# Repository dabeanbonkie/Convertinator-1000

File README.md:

# Convertinator 1000 Showcase

# Description
The Convertinator 1000 is a basic power supply that converts voltage from a USB-C (5V) to 1.2V, 3.3V, 12V & 24V, also featuring an output for 5V. It has the input as the USB-C and the outputs as dupont headers as its main use is for prototyping small cicuits and basic breadboarding. It isnt made to handle strong current but the 12V & 24V connections should be able to handle a bit more.

# Reason
I designed this as a project that i could maybe use in the future when doing smaller projects as i get more and more proficient in hardware. Its not intended to run anything too heavy but can handle basic circuitly which is all I would need it for. It also worked perfectly as a project to do while parts for other projects were printing.

# Usage
To use the Convertinator 1000, take a USB-C plugged into any socket (as long as it supplies 5V) and plug it into the USB-C component on the Convertinator 1000. From there, take two dupont wires and connect them to the two headers for each voltage. One header is for the output voltage which on each connection is the header on the left, and the other is the ground which is always on the right. I highly advise you NOT to run anything above 1A on the 1.2V, 3.3V & 5V headers and NOT anything above 1.8A on the 12V & 24V headers.

# Assembly
Putting all the parts together is easy as can be. Since i figured this power supply wouldnt be moving much i havent mounted the pcb. So to assemble the Convertinator 1000, just print both components, put the pcb in the shell making sure all the gubbins on the bottom of the pcb cleanly fit into the groves on the bottom of the shell. Then mount the lid to the shell using a simple nut and bolt (4.8 mm) on the mounting holes on both parts. Then its all complete.

Here is how the pcb should be placed from the bottom of the shell:

# PCB schematic

# PCB editor 

# Onshape Link
https://cad.onshape.com/documents/8818f429682032fa239a6543/w/3c67bc1c1aed2304218f7515/e/04401e7b527ba54e698f04d5?renderMode=0&uiState=6a372eb3d7346ceef4239fb8

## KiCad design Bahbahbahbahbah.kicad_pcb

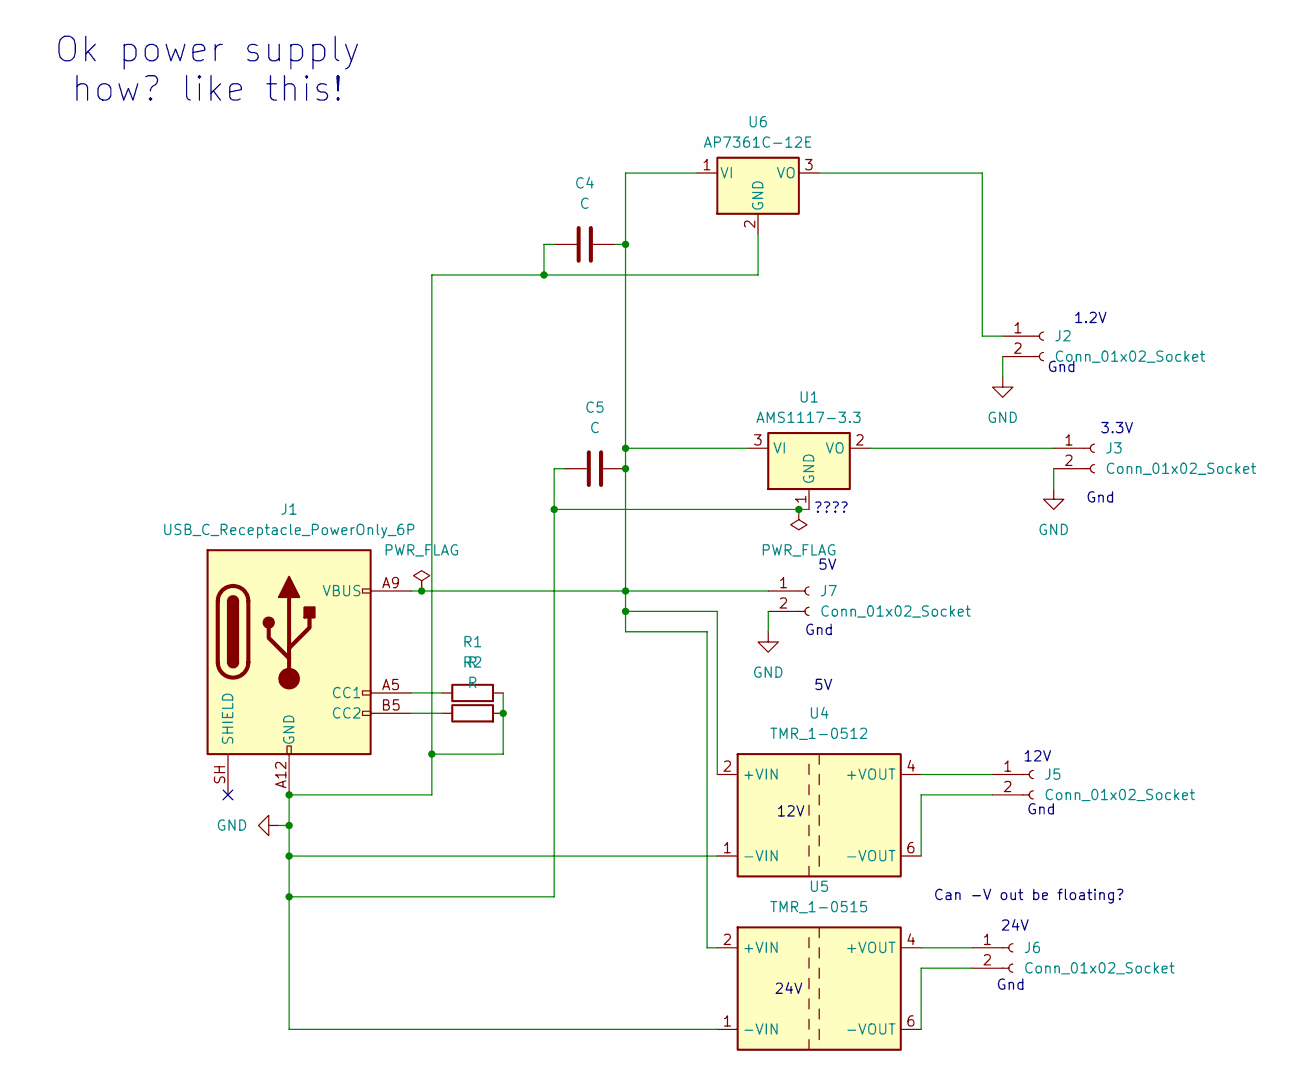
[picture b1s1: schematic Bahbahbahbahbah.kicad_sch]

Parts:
C4, C5: C; C_0402_1005Metric
J1: USB_C_Receptacle_PowerOnly_6P; USB_C_Receptacle_GCT_USB4125-xx-x-0190_6P_TopMnt_Horizontal
J2, J3, J5, J6, J7: Conn_01x02_Socket; PinSocket_1x02_P2.54mm_Horizontal
R1, R2: R; R_0402_1005Metric
U1: AMS1117-3.3; SOT-223-3_TabPin2
U4: TMR_1-0512; Converter_DCDC_TRACO_TMR-1-xxxx_Single_THT
U5: TMR_1-0515; Converter_DCDC_TRACO_TMR-1-xxxx_Single_THT
U6: AP7361C-12E; SOT-223-3_TabPin2

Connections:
GND: C4.1, C5.1, J1.A12 (GND), J1.B12 (GND), J2.2, J3.2, J7.2, R1.2, R2.2, U1.1 (GND), U4.1 (-VIN), U5.1 (-VIN), U6.2 (GND)
unnamed: J1.A5 (CC1), R1.1
unnamed: J1.B5 (CC2), R2.1
unnamed: J2.1, U6.3 (VO)
unnamed: J3.1, U1.2 (VO)
unnamed: J5.1, U4.4 (+VOUT)
unnamed: J5.2, U4.6 (-VOUT)
unnamed: J6.1, U5.4 (+VOUT)
unnamed: J6.2, U5.6 (-VOUT)
unnamed: C4.2, C5.2, J1.A9 (VBUS), J1.B9 (VBUS), J7.1, U1.3 (VI), U4.2 (+VIN), U5.2 (+VIN), U6.1 (VI)

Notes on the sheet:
Can -V out be floating?
Ok power supply how? like this!
????
Gnd
12V
1.2V
3.3V
24V

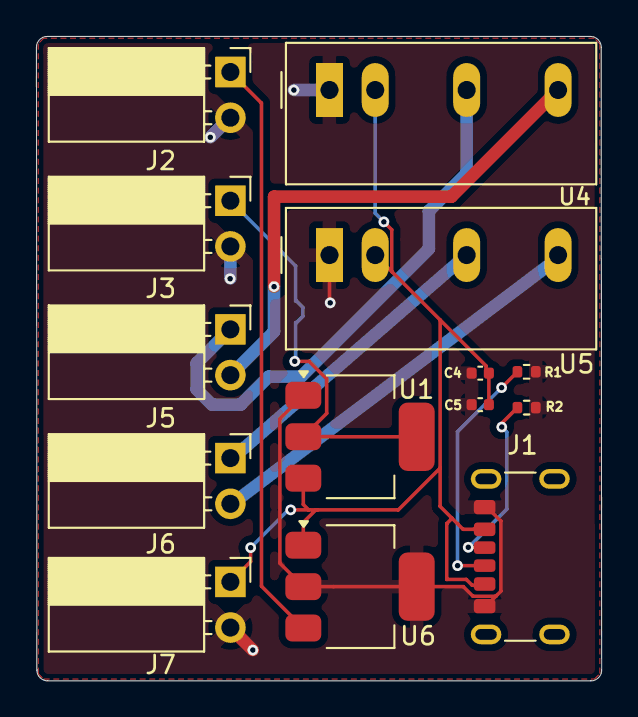
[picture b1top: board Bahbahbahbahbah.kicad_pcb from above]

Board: 2 copper layers, 31.4 x 35.8 mm, 14 parts (0 on the bottom side), 10 nets.

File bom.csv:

Designator,Footprint,Quantity,Value,LCSC Part #
"C4, C5",0201,2,C,
J1,USB_C_Receptacle_GCT_USB4125-xx-x-0190_6P_TopMnt_Horizontal,1,USB_C_Receptacle_PowerOnly_6P,
"J2, J3, J5, J6, J7",PinSocket_1x02_P2.54mm_Horizontal,5,Conn_01x02_Socket,
U1,SOT-223-3_TabPin2,1,AMS1117-3.3,
U4,Converter_DCDC_TRACO_TMR-1-xxxx_Single_THT,1,TMR_1-0512,
U5,Converter_DCDC_TRACO_TMR-1-xxxx_Single_THT,1,TMR_1-0515,
U6,SOT-223-3_TabPin2,1,AP7361C-12E,

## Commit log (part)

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2026-06-20 Create STL- Files Shell & Lid Convertinator 1000
2026-06-21 Create PCB Gerber files Convertinator-1000
